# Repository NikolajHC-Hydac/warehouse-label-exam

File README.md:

<div id="top"></div>

<!-- PROJECT LOGO -->
<br />
<div align="center">

<h3 align="center">Hydac DK Digital 1.0</h3>

  <p align="center">
    Box divided storage system controlled with buttons 
    <br />
    <a href="https://github.com/HydacDK/New-Warehouse-Lables/tree/Prototype4"><strong>Explore the docs »</strong></a>
    <br />
    <br />
    <a href="https://github.com/HydacDK/New-Warehouse-Lables/tree/Prototype4">View Demo</a>
    ·
    <a href="https://github.com/HydacDK/New-Warehouse-Lables/tree/Prototype4/issues">Report Bug</a>
    ·
    <a href="https://github.com/HydacDK/New-Warehouse-Lables/tree/Prototype4/issues">Request Feature</a>
  </p>
</div>

<!-- TABLE OF CONTENTS -->
<details>
  <summary>Table of Contents</summary>
  <ol>
    <li>
      <a href="#about-the-project">About The Project</a>
      <ul>
        <li><a href="#built-with">Built With</a></li>
      </ul>
    </li>
    <li>
      <a href="#getting-started">Getting Started</a>
      <ul>
        <li><a href="#prerequisites">Prerequisites</a></li>
        <li><a href="#installation">Installation</a></li>
      </ul>
    </li>
    <li><a href="#usage">Usage</a></li>
    <li><a href="#roadmap">Roadmap</a></li>
    <li><a href="#contact">Contact</a></li>
  </ol>
</details>

<!-- ABOUT THE PROJECT -->
## About The Project

[![Product Name Screen Shot][product-screenshot]](http://localhost:1880/ui)

A simple box divided storage system, where two similar boxes with goods are placed on shelves. Buttons are placed on the front and back of the shelves, 2 push buttons for each pair of boxes. When a box is empty, the user presses the "order" on the front of the shelf, and the system notes on the reorder list that the box needs to be refilled. Once a week, the purchasing department will get a list of what c-items (bolts, washers and nuts) that needs to be ordered

Part goal:
C-items (bolts, washers and nuts) are ordered semi automatically by the user, system notes on the reorder list and sends it to the purchasing department weekly. Goods are stocked directly on the shelf.

Goal:
C-items (bolts, washers and nuts) ordered semi automatically by the user, and is sent directly to the distributor of said item. Items stocked directly on the shelf, and ready to use, without the purchasing department using resources on the process. Every month, the purchasing department will receive an invoice, while responsibility for the stock is outsourced to the user.

Gain:
It provides gain on all shelves: Purchasing, finance and user have fewer hours of administration in connection with ordering, invoicing, status, etc. Warehouse spends less time on transport to and from the warehouse and less time on searching for the goods. In addition, the standard program always contains the relevant items in appropriate quantities, and we can therefore cut back on both purchasing and stock binding.

<p align="right">(<a href="#top">back to top</a>)</p>

### Built With

* [Node-red](https://nodered.org/)
* [C++](https://isocpp.org/)
* [SQLite](https://www.sqlite.org/index.html)

<p align="right">(<a href="#top">back to top</a>)</p>

<!-- GETTING STARTED -->
## Getting Started

To get a local copy up and running follow these simple steps.

### Prerequisites

#### Debian and ubuntu based linux distributions  

* Node.js / npm
  ```sh
  # Using Ubuntu  
  curl -fsSL https://deb.nodesource.com/setup_14.x | sudo -E bash -
  sudo apt-get install -y nodejs

  # Using Debian, as root
  curl -fsSL https://deb.nodesource.com/setup_14.x | bash -
  apt-get install -y nodejs
  ```

* Node-red
  ```sh
  sudo npm install -g --unsafe-perm node-red
  ```  

#### Windows

* Node.js
  ```markdown
  Download a 64 or 32 bit version of node.js at [https://nodejs.org](https://nodejs.org/download/release/v14.19.1/)  
  Run the downloaded MSI file.  
    
  Once installed, open a command prompt and run the following command to ensure Node.js and npm are installed correctly.

  Using Powershell: node --version; npm --version

  Using cmd: node --version && npm --version
  ```  

* Node-red
  ```sh
  npm install -g --unsafe-perm node-red
  ```

### Installation

1. Clone the repo
   ```sh
   git clone https://github.com/HydacDK/New-Warehouse-Lables/tree/Prototype4.git
   ```
2. Build and upload esp32 code to control board 
3. Start node-red
    ```sh
    node-red
    ```
4. Import the "Flows.json" file using the node-red GUI
5. Install missing node-red modules
6. Set up mqtt server in the "MQTT" flow
7. In the "Database" flow, point the sqlite and watch nodes to the location of warehouselabels.db
8. Go to http://localhost:1880/ui, or wherever your node-red instance is hosted, enter the setup page, and add the email you want to receive updates on.

<p align="right">(<a href="#top">back to top</a>)</p>

<!-- USAGE EXAMPLES -->
## Usage

![TestStand][test-stand]

Buttons are placed in the front of every box pair on shelves, as well as behind them.  
Product numbers are then added to the database, and paired with their respective buttons, either by manually adding them using the setup page in the UI, or by importing them using a CSV file.  
When a box has been emptied, the user presses the matching front button once, and puts the box back in the back of the shelf.  
When the boxes are refilled, the user that is refilling the box, presses the matching button on the back of the shelf, to indicate to the system that the box has been filled again.

_For more examples, please refer to the [Documentation](https://example.com)_

<p align="right">(<a href="#top">back to top</a>)</p>

<!-- ROADMAP -->
## Roadmap

- [x] LED's on front buttons, showing the inventory status to the user
- [x] Automated opening of the UI after a system reset
- [x] Control board revision 4 PCB
    - [x] Design
    - [x] Order
    - [ ] Test
- [x] Buttons PCB
    - [x] Design
    - [x] Order
    - [x] Test

See the [open issues](https://github.com/HydacDK/New-Warehouse-Lables/issues) for a full list of proposed features (and known issues).

<p align="right">(<a href="#top">back to top</a>)</p>

<!-- CONTACT -->
## Contact

Linkedin: Nikolaj Hult-Christensen - [/in/nikolajhult](https://linkedin.com/in/nikolajhult)  
Email: Nikolaj.Hult-Christensen@hydac.dk  
Element: @hultn:hydac.com

Project Link: [https://github.com/HydacDK/New-Warehouse-Lables/tree/Prototype4](https://github.com/HydacDK/New-Warehouse-Lables/tree/Prototype4)

<p align="right">(<a href="#top">back to top</a>)</p>

<!-- MARKDOWN LINKS & IMAGES -->
<!-- https://www.markdownguide.org/basic-syntax/#reference-style-links -->
[contributors-shield]: https://img.shields.io/github/contributors/HydacDK/New-WarehouseLabels.svg?style=for-the-badge
[contributors-url]: https://github.com/HydacDK/New-WarehouseLabels/graphs/contributors
[forks-shield]: https://img.shields.io/github/forks/HydacDK/New-Warehouse-Lables/tree/Prototype4.svg?style=for-the-badge
[forks-url]: https://github.com/HydacDK/New-Warehouse-Lables/tree/Prototype4/network/members
[stars-shield]: https://img.shields.io/github/stars/HydacDK/New-Warehouse-Lables/tree/Prototype4.svg?style=for-the-badge
[stars-url]: https://github.com/HydacDK/New-Warehouse-Lables/tree/Prototype4/stargazers
[issues-shield]: https://img.shields.io/github/issues/HydacDK/New-Warehouse-Lables/tree/Prototype4.svg?style=for-the-badge
[issues-url]: https://github.com/HydacDK/New-Warehouse-Lables/tree/Prototype4/issues
[license-shield]: https://img.shields.io/github/license/HydacDK/New-Warehouse-Lables/tree/Prototype4.svg?style=for-the-badge
[license-url]: https://github.com/HydacDK/New-Warehouse-Lables/tree/Prototype4/blob/master/LICENSE.txt
[linkedin-shield]: https://img.shields.io/badge/-LinkedIn-black.svg?style=for-the-badge&logo=linkedin&colorB=555
[linkedin-url]: https://linkedin.com/in/linkedin_username
[product-screenshot]: images/screenshot.png
[test-stand]: images/teststand.jpg

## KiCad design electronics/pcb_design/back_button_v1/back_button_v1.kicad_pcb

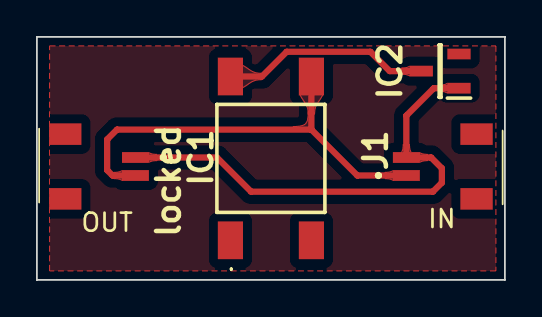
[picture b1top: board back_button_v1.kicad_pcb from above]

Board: 2 copper layers, 26.0 x 13.5 mm, 4 parts (0 on the bottom side), 3 nets.

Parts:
IC1: TS04-66-73-BK-260-SMT; TS046673BK160SMT
IC2: DS28E05R+T; SOT95P237X112-3N
J1: 202396-0207; 2023960207
locked: 202396-0207; 2023960207

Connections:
unnamed: IC1.3 (NO_2), IC2.3 (GND)
unnamed: IC1.4 (COM_2), J1.1, locked.2
unnamed: IC2.1 (IO), J1.2, locked.1

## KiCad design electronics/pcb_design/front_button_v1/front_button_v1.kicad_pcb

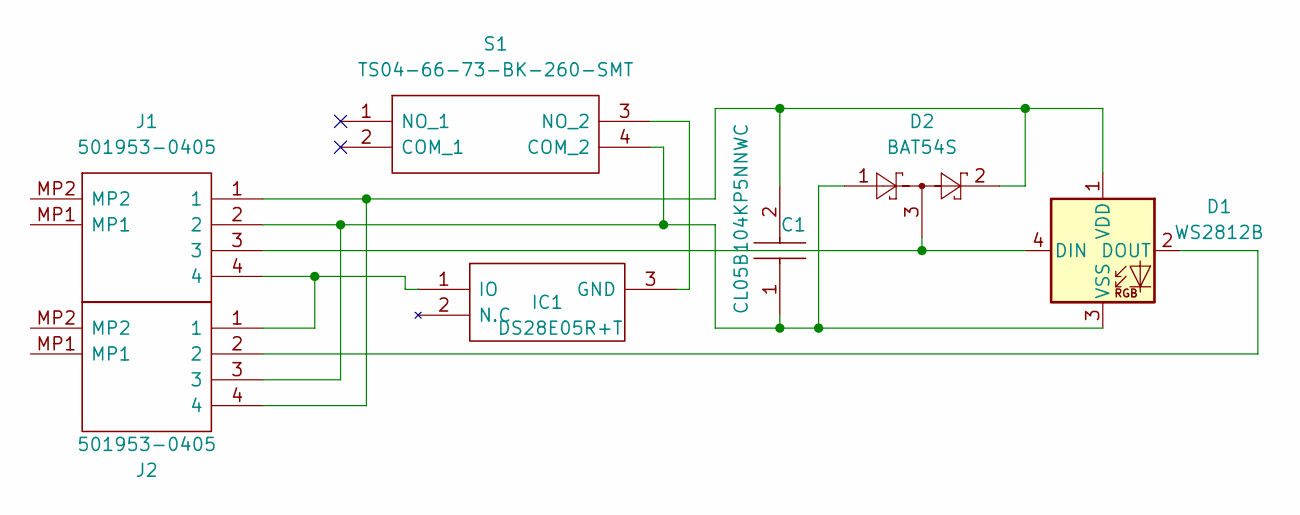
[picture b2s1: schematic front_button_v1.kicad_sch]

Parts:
C1: CL05B104KP5NNWC; CAPC1005X55N; Manufacturer_Part_Number CL05B104KP5NNWC
D1: WS2812B; LED_WS2812B_PLCC4_5.0x5.0mm_P3.2mm
D2: BAT54S; SOT-23
IC1: DS28E05R+T; SOT95P237X112-3N; Mouser Part Number 700-DS28E05R+T
J1, J2: 501953-0405; 5019530405; Mouser Part Number 538-501953-0405
S1: TS04-66-73-BK-260-SMT; TS046673BK160SMT; Manufacturer_Part_Number TS04-66-73-BK-160-SMT; Mouser Part Number 179-TS046673BK160SMT

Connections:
unnamed: C1.1, D1.3 (VSS), D2.1, J1.2, J2.3, S1.4 (COM_2)
unnamed: C1.2, D1.1 (VDD), D2.2, J1.1, J2.4
unnamed: D1.2 (DOUT), J2.2
unnamed: D1.4 (DIN), D2.3, J1.3
unnamed: IC1.1 (IO), J1.4, J2.1
unnamed: IC1.3 (GND), S1.3 (NO_2)

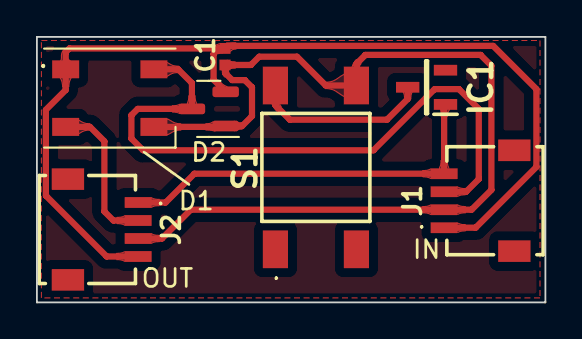
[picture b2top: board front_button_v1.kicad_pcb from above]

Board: 2 copper layers, 28.2 x 14.8 mm, 7 parts (0 on the bottom side), 6 nets.

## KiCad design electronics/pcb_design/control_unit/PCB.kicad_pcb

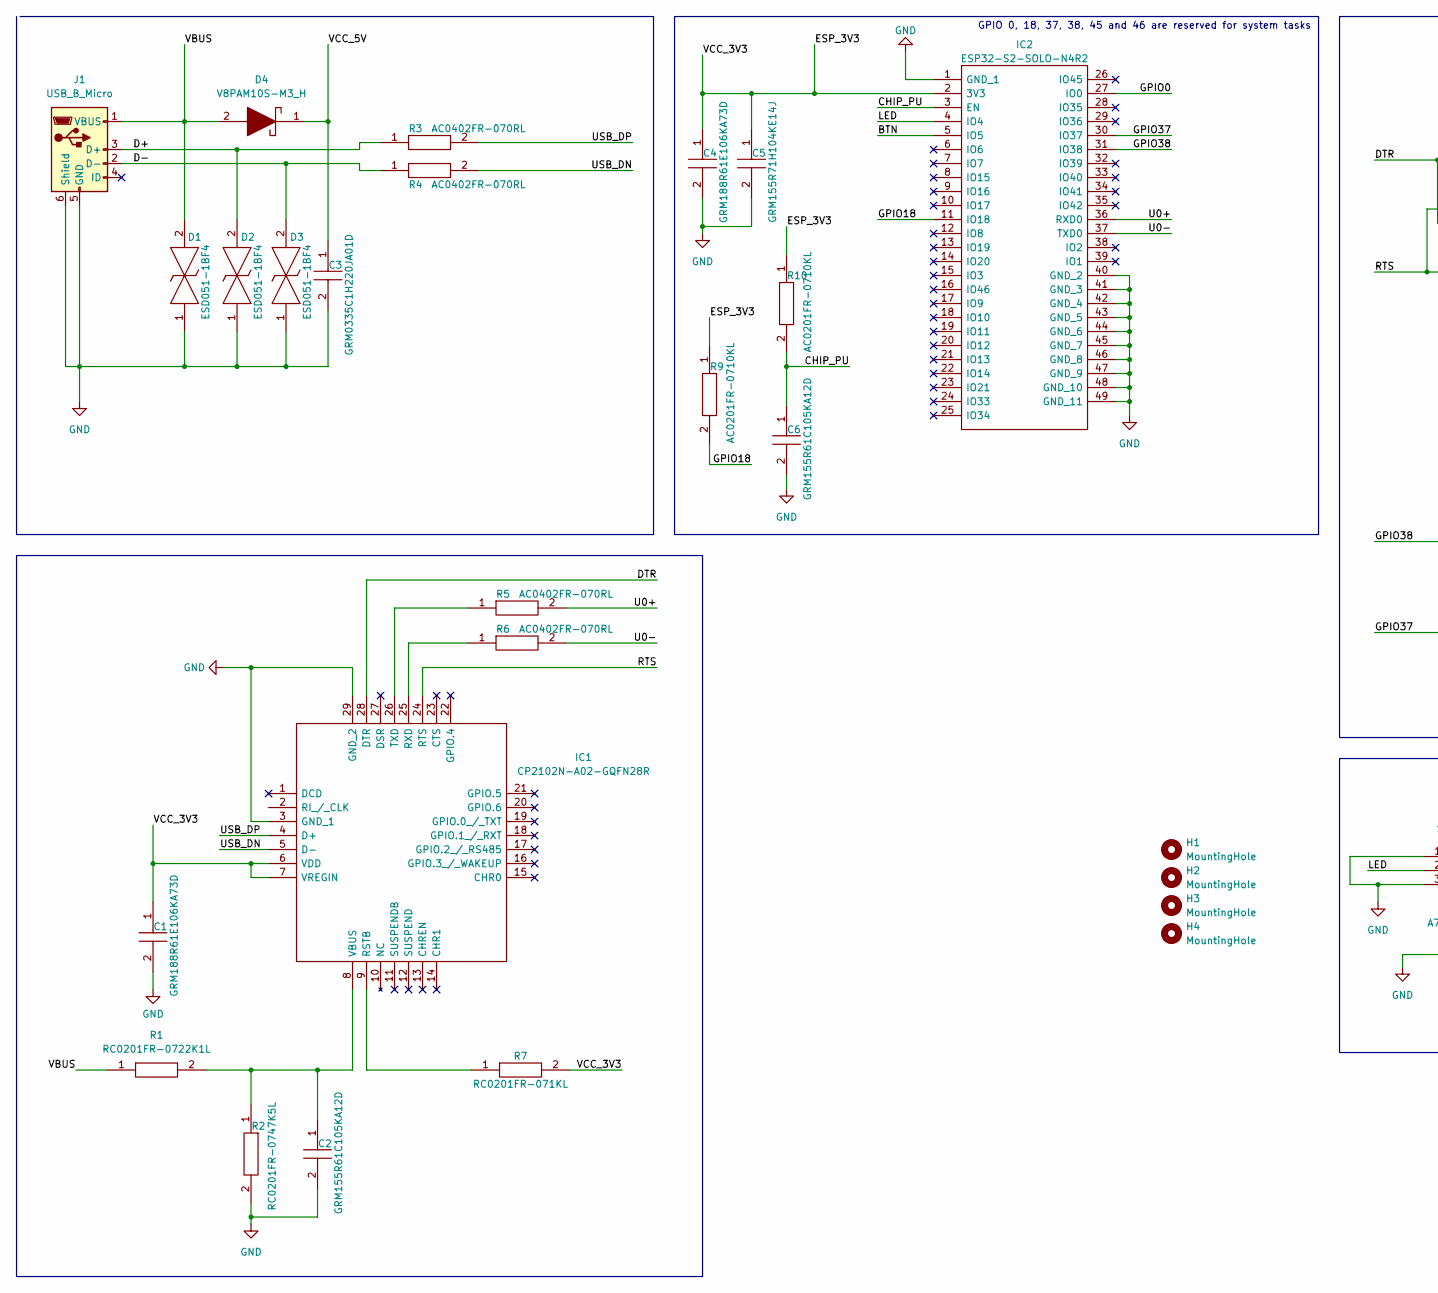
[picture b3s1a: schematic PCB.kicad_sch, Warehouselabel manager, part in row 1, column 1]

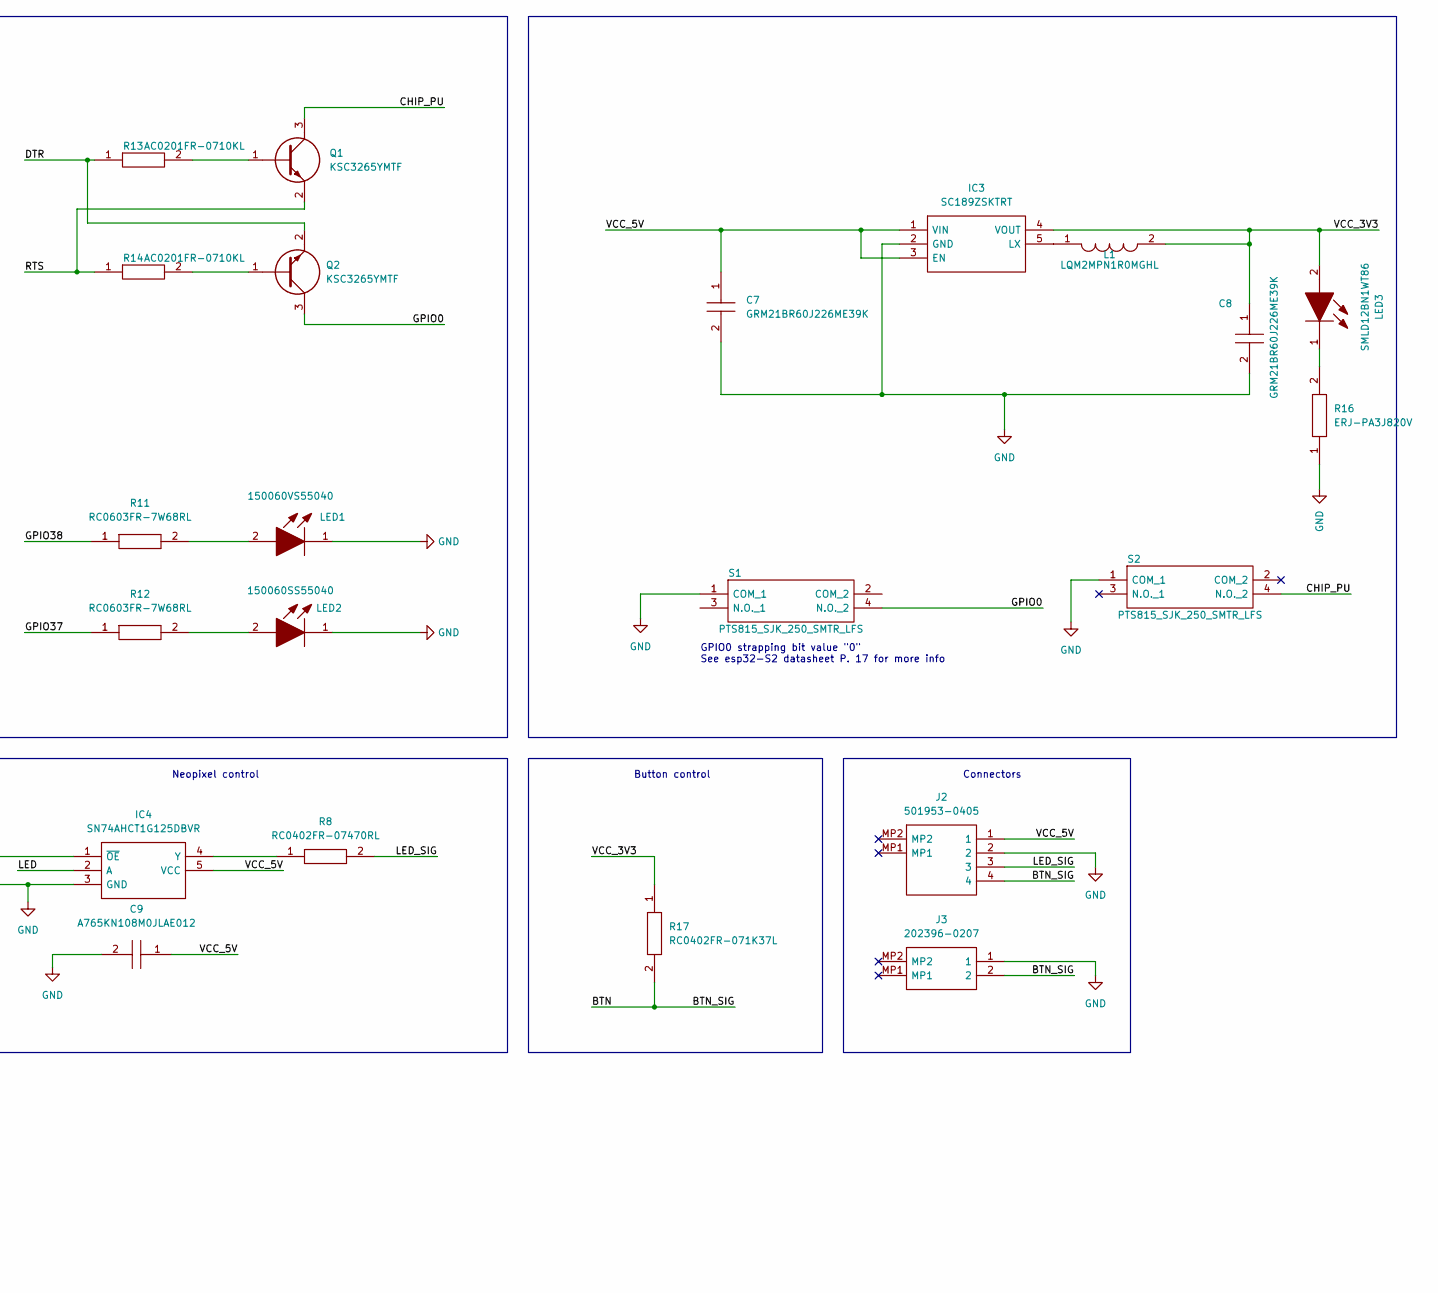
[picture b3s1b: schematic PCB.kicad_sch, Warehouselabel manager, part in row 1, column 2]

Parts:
C1, C4: GRM188R61E106KA73D; CAPC1608X90N; Mouser Part Number 81-GRM188R61E106KA3D
C2, C6: GRM155R61C105KA12D; CAPC1005X55N; Mouser Part Number 81-GRM155R61C105KA2D
C3: GRM0335C1H220JA01D; CAPC0603X33N; Mouser Part Number 81-GRM0335C1H220JA1D
C5: GRM155R71H104KE14J; CAPC1005X55N; Mouser Part Number 81-GRM155R71H104KE4J
C7, C8: GRM21BR60J226ME39K; CAPC2012X140N; Mouser Part Number 81-GRM21BR60J226ME9K
C9: A765KN108M0JLAE012; CAPAE830X1000N; Manufacturer_Part_Number A765KN108M0JLAE012
D1, D2, D3: ESD051-1BF4; ESD0511BF4; Mouser Part Number 511-ESD051-1BF4
D4: V8PAM10S-M3_H; V8PAM10SHM3H; Mouser Part Number 78-V8PAM10S-M3/H
H1, H2, H3, H4: MountingHole; MountingHole_2.7mm_M2.5_ISO7380
IC1: CP2102N-A02-GQFN28R; QFN50P500X500X80-29N-D; Mouser Part Number 634-CP2102NA02QFN28R
IC2: ESP32-S2-SOLO-N4R2; ESP32S2SOLON4R2; Mouser Part Number 356-ESP32-S2SOLON4R2
IC3: SC189ZSKTRT; SOT95P280X145-5N; Mouser Part Number 947-SC189ZSKTRT
IC4: SN74AHCT1G125DBVR; SOT95P280X145-5N; Mouser Part Number 595-SNAHCT1G125DBVR
J1: USB_B_Micro; USB_Micro-B_Amphenol_10104110_Horizontal
J2: 501953-0405; 5019530405; Mouser Part Number 538-501953-0405
J3: 202396-0207; 2023960207; Mouser Part Number 538-202396-0207
L1: LQM2MPN1R0MGHL; LQM2MPN1R0NG0L; Mouser Part Number 81-LQM2MPN1R0MGHL
LED1: 150060VS55040; LEDM168X50N; Mouser Part Number 710-150060VS55040
LED2: 150060SS55040; Mouser Part Number 710-150060SS55040
LED3: SMLD12BN1WT86; LEDM168X65N; Mouser Part Number 755-SMLD12BN1WT86
Q1, Q2: KSC3265YMTF; SOT96P237X111-3N; Mouser Part Number 512-KSC3265YMTF
R1: RC0201FR-0722K1L; RESC0603X26N; Mouser Part Number 603-RC0201FR-0722K1L
R2: RC0201FR-0747K5L; RESC0603X26N; Mouser Part Number 603-RC0201FR-0747K5L
R3, R4, R5, R6: AC0402FR-070RL; RESC1005X37N; Mouser Part Number 603-AC0402FR-070RL
R7: RC0201FR-071KL; RESC0603X26N; Mouser Part Number 603-RC0201FR-071KL
R8: RC0402FR-07470RL; RESC1005X40N; Mouser Part Number 603-RC0402FR-07470RL
R9, R10, R13, R14: AC0201FR-0710KL; RESC0603X26N; Mouser Part Number 603-AC0201FR-0710KL
R11, R12: RC0603FR-7W68RL; RESC1608X55N; Manufacturer_Part_Number RC0603FR-7W68RL
R16: ERJ-PA3J820V; R_0603_1608Metric; Manufacturer_Part_Number ERJ-PA3J820V
R17: RC0402FR-071K37L; RESC1005X40N; Manufacturer_Part_Number RC0402FR-071K37L
S1, S2: PTS815_SJK_250_SMTR_LFS; PTS815SJK250SMTRLFS; Mouser Part Number 611-PTS815SJK250SMTR

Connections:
/BTN: IC2.5 (IO5), J2.4, J3.2, R17.2
/CHIP_PU: C6.1, IC2.3 (EN), Q1.3, R10.2, S2.4 (N.O._2)
/D+: D2.2, J1.3 (D+), R3.1
/D-: D3.2, J1.2 (D-), R4.1
/DTR: IC1.28 (DTR), Q2.2, R13.1
/ESP_3V3: C1.1, C4.1, C5.1, C8.1, IC1.6 (VDD), IC1.7 (VREGIN), IC2.2 (3V3), IC3.4 (VOUT), L1.2, LED3.2, R7.2, R9.1, R10.1, R17.1
/GPIO0: IC2.27 (IO0), Q2.3, S1.4 (N.O._2)
/GPIO18: IC2.11 (IO18), R9.2
/GPIO37: IC2.30 (IO37), R12.1
/GPIO38: IC2.31 (IO38), R11.1
/LED: IC2.4 (IO4), IC4.2 (A)
/LED_SIG: J2.3, R8.2
/RTS: IC1.24 (RTS), Q1.2, R14.1
/U0+: IC2.36 (RXD0), R5.2
/U0-: IC2.37 (TXD0), R6.2
/USB_DN: IC1.5 (D-), R4.2
/USB_DP: IC1.4 (D+), R3.2
/VBUS: D1.2, D4.2, J1.1 (VBUS), R1.1
/VCC_5V: C3.1, C7.1, C9.1, D4.1, IC3.1 (VIN), IC3.3 (EN), IC4.5 (VCC), J2.1
GND: C1.2, C2.2, C3.2, C4.2, C5.2, C6.2, C7.2, C8.2, C9.2, D1.1, D2.1, D3.1, IC1.3 (GND_1), IC1.29 (GND_2), IC2.1 (GND_1), IC2.40 (GND_2), IC2.41 (GND_3), IC2.42 (GND_4), IC2.43 (GND_5), IC2.44 (GND_6), IC2.45 (GND_7), IC2.46 (GND_8), IC2.47 (GND_9), IC2.48 (GND_10), IC2.49 (GND_11), IC3.2 (GND), IC4.1 (~OE), IC4.3 (GND), J1.5 (GND), J1.6 (Shield), J2.2, J3.1, LED1.1, LED2.1, R2.2, R16.1, S1.1 (COM_1), S2.1 (COM_1)
unnamed: C2.1, IC1.8 (VBUS), R1.2, R2.1
unnamed: IC1.9 (RSTB), R7.1
unnamed: IC1.25 (RXD), R6.1
unnamed: IC1.26 (TXD), R5.1
unnamed: IC3.5 (LX), L1.1
unnamed: IC4.4 (Y), R8.1
unnamed: LED1.2, R11.2
unnamed: LED2.2, R12.2
unnamed: LED3.1, R16.2
unnamed: Q1.1, R13.2
unnamed: Q2.1, R14.2

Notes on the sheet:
Button control
Neopixel control
GPIO0 strapping bit value "0" See esp32-S2 datasheet P. 17 for more info
GPIO 0, 18, 37, 38, 45 and 46 are reserved for system tasks
Connectors

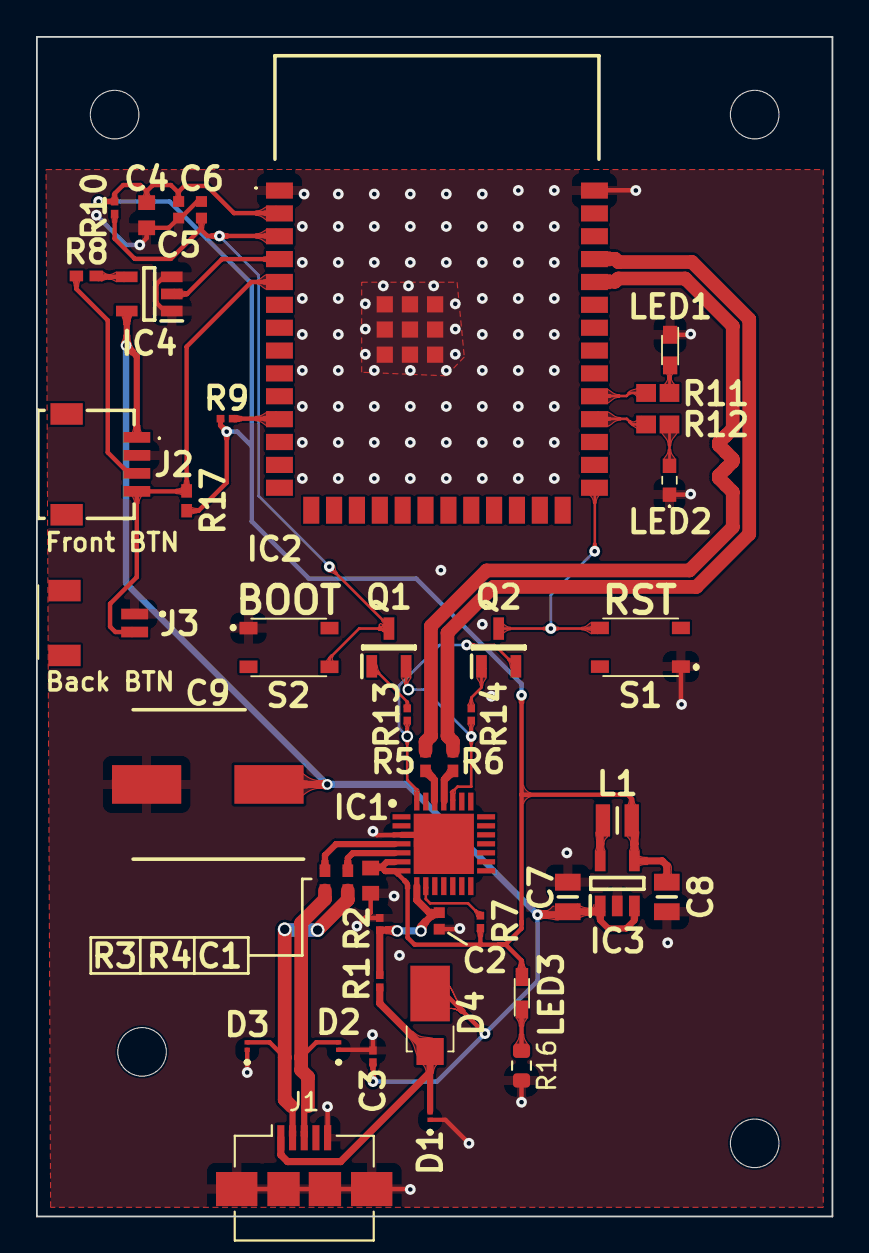
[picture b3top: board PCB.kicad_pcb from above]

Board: 2 copper layers, 44.2 x 65.5 mm, 48 parts (0 on the bottom side), 31 nets.

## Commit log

2022-06-10 Copy private repo
    Copy private repo to make it public for exam
